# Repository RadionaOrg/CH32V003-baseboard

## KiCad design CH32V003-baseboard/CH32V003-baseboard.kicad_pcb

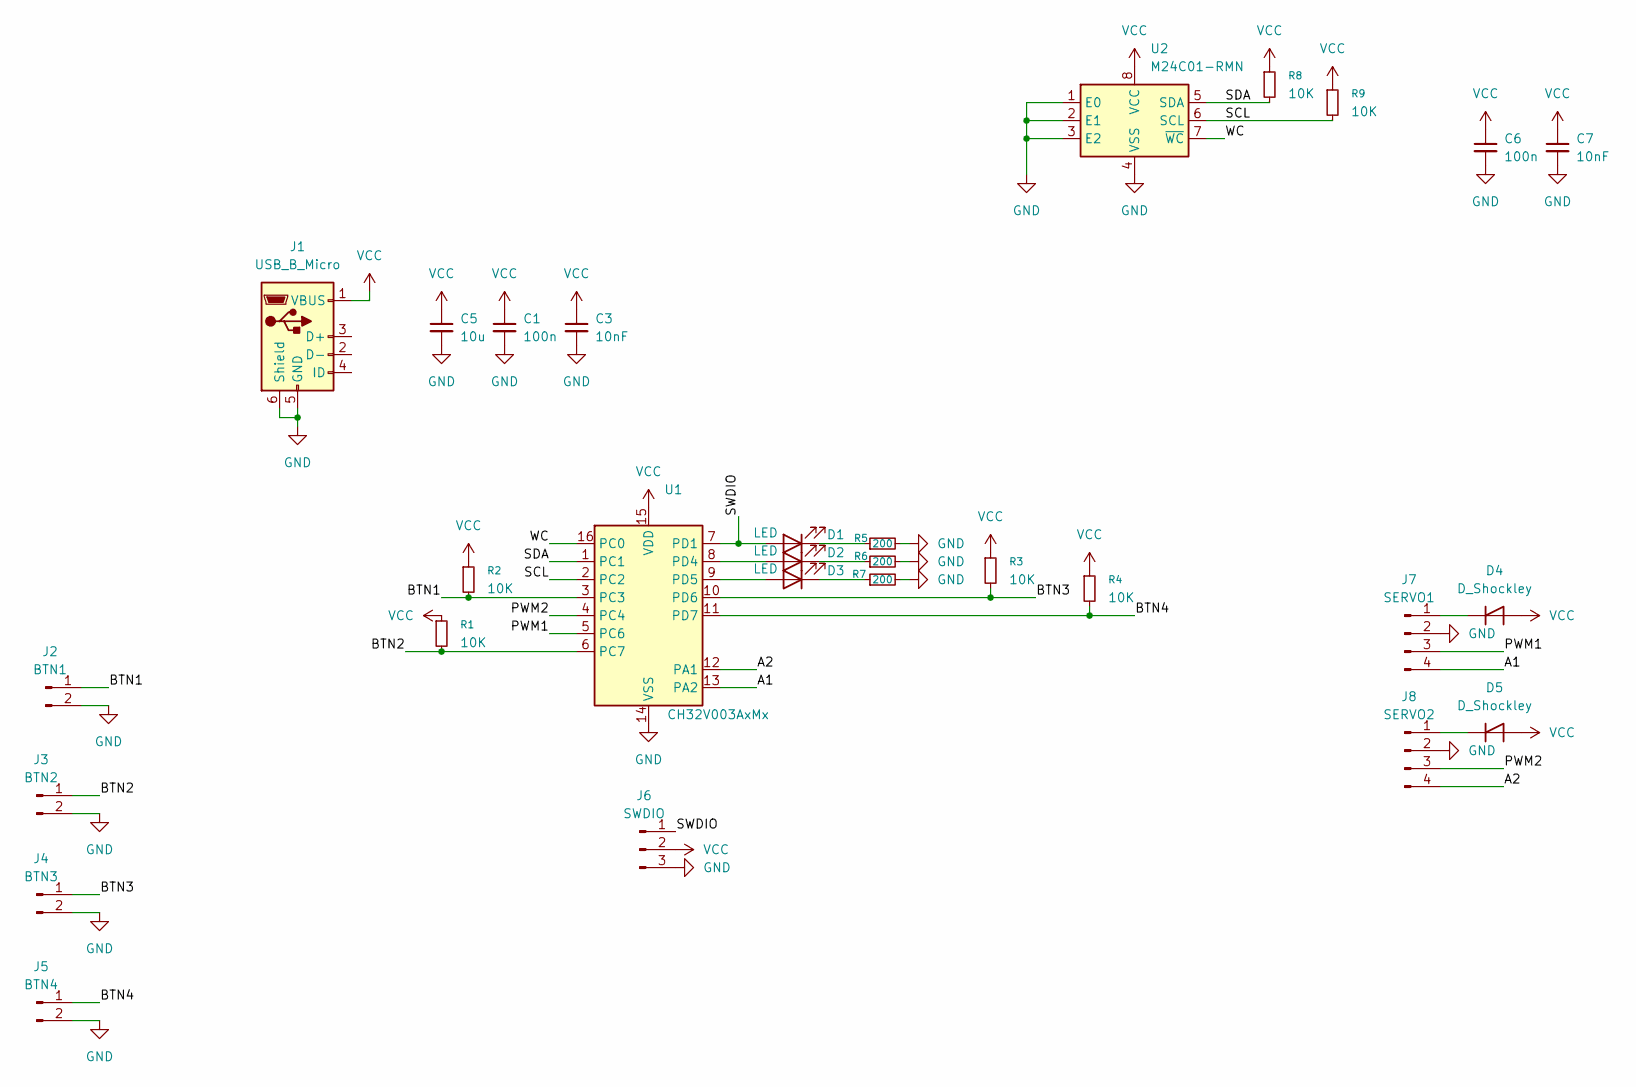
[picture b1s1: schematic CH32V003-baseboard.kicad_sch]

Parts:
C1, C6: 100n; C_0603_1608Metric_Pad1.08x0.95mm_HandSolder
C3, C7: 10nF; C_0603_1608Metric_Pad1.08x0.95mm_HandSolder
C5: 10u; C_0603_1608Metric_Pad1.08x0.95mm_HandSolder
D1, D2, D3: LED; LED_0603_1608Metric_Pad1.05x0.95mm_HandSolder
D4, D5: D_Shockley; D_0603_1608Metric
J1: USB_B_Micro; USB_Micro-B_Wuerth_629105150521
J2: BTN1; PinSocket_1x02_P2.54mm_Vertical
J3: BTN2; PinSocket_1x02_P2.54mm_Vertical
J4: BTN3; PinSocket_1x02_P2.54mm_Vertical
J5: BTN4; PinSocket_1x02_P2.54mm_Vertical
J6: SWDIO; PinSocket_1x03_P2.54mm_Vertical
J7: SERVO1; PinSocket_1x04_P2.54mm_Vertical
J8: SERVO2; PinSocket_1x04_P2.54mm_Vertical
R1, R2, R3, R4, R8, R9: 10K; R_0603_1608Metric_Pad0.98x0.95mm_HandSolder
R5, R6, R7: 200; R_0603_1608Metric_Pad0.98x0.95mm_HandSolder
U1: CH32V003AxMx; SOP-16_3.9x9.9mm_P1.27mm
U2: M24C01-RMN; SOIC-8_3.9x4.9mm_P1.27mm

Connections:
/A1: J7.4, U1.13 (PA2)
/A2: J8.4, U1.12 (PA1)
/BTN1: J2.1, R2.2, U1.3 (PC3)
/BTN2: J3.1, R1.2, U1.6 (PC7)
/BTN3: J4.1, R3.2, U1.10 (PD6)
/BTN4: J5.1, R4.2, U1.11 (PD7)
/PWM1: J7.3, U1.5 (PC6)
/PWM2: J8.3, U1.4 (PC4)
/SCL: R9.2, U1.2 (PC2), U2.6 (SCL)
/SDA: R8.2, U1.1 (PC1), U2.5 (SDA)
/SWDIO: D1.2 (A), J6.1, U1.7 (PD1)
/WC: U1.16 (PC0), U2.7 (~WC)
GND: C1.2, C3.2, C5.2, C6.2, C7.2, J1.5 (GND), J1.6 (Shield), J2.2, J3.2, J4.2, J5.2, J6.3, J7.2, J8.2, R5.2, R6.2, R7.2, U1.14 (VSS), U2.1 (E0), U2.2 (E1), U2.3 (E2), U2.4 (VSS)
unnamed: D1.1 (K), R5.1
unnamed: D2.2 (A), U1.8 (PD4)
unnamed: D2.1 (K), R6.1
unnamed: D3.2 (A), U1.9 (PD5)
unnamed: D3.1 (K), R7.1
unnamed: D4.1 (K), J7.1
unnamed: D5.1 (K), J8.1
VCC: C1.1, C3.1, C5.1, C6.1, C7.1, D4.2 (A), D5.2 (A), J1.1 (VBUS), J6.2, R1.1, R2.1, R3.1, R4.1, R8.1, R9.1, U1.15 (VDD), U2.8 (VCC)

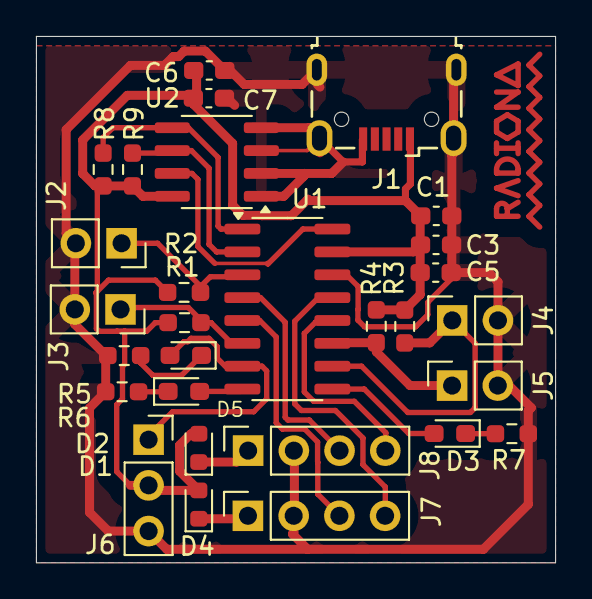
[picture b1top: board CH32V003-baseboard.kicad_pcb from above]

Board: 2 copper layers, 28.8 x 29.2 mm, 30 parts (0 on the bottom side), 21 nets.

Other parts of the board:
radiona: radiona

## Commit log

2025-07-15 initial version
